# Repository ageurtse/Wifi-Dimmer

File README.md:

# Wifi Dimmer

!!!!! Please do not rebuild this device, in my case there was a serious issue with overheating !!!!!

This is all about my home build WiFi Dimmer
Becaus of it's my first github project, the master is still in Beta. 
For me the project works, but there are a lot off things to change, so keep watching for any change.

11-3-2019, final version, the hard and software is ready to use. 
soon i wil post a youtube movie from live controlling a light. 

This is version 2, in the past i build a differt version which is not exactly what i want. 
Version 2 is one which fit in a simpel housing. 

There are 2 parts of the software, one for the ATTiny and one for the ESP8266
Both are posted here. 
# Word of Caution
Please be very carefull you are working with live voltage 230V, this voltage can realy harm you. 
By building the dimmer, i'm not responsible for any faults or what ever. I stoped development off this dimmer, on one night the triax was overheated. luckely i was at home to prevented real major damage. 

# ATtiny85 Software
The ATtiny85 software is for the soul purpose of dimming the light, there is a zerocross detction which is on interupt 0, the gate is on pin PB3. 
The communication with the main processor is done by softserial. 
The code is based on the forum post at arduino : https://forum.arduino.cc/index.php?topic=314773.0

# ESP8266 software
The main software for the ESP12 module is build with arduino, the wifi and custom settings can be done with the great library from Hieromon https://github.com/Hieromon/AutoConnect
After fist flash by serial, all next updates could be down by browser. 
find the IP-adres or host name and add /update to get to the update page. 
To alter wifi setting's and in the futher mqtt settings and i hope a lot more add /_ac

The file makes use of some thirth party library's which can be found here :
AutoConnect : https://github.com/Hieromon/AutoConnect
PageBuilder : https://github.com/Hieromon/PageBuilder
ArduinoJson : https://arduinojson.org/ version 5

# The hardware
For the main board there is a small mistake made with the Triac, there where 2 wires changes. A1 and A2 need to be turned. 
In a next updat of the print i will fix that, for now i just solderd 2 wires and cross connect them to te pcb.

Also the Fuse holder is to large, i bought a pcb fuse now it all fits well.

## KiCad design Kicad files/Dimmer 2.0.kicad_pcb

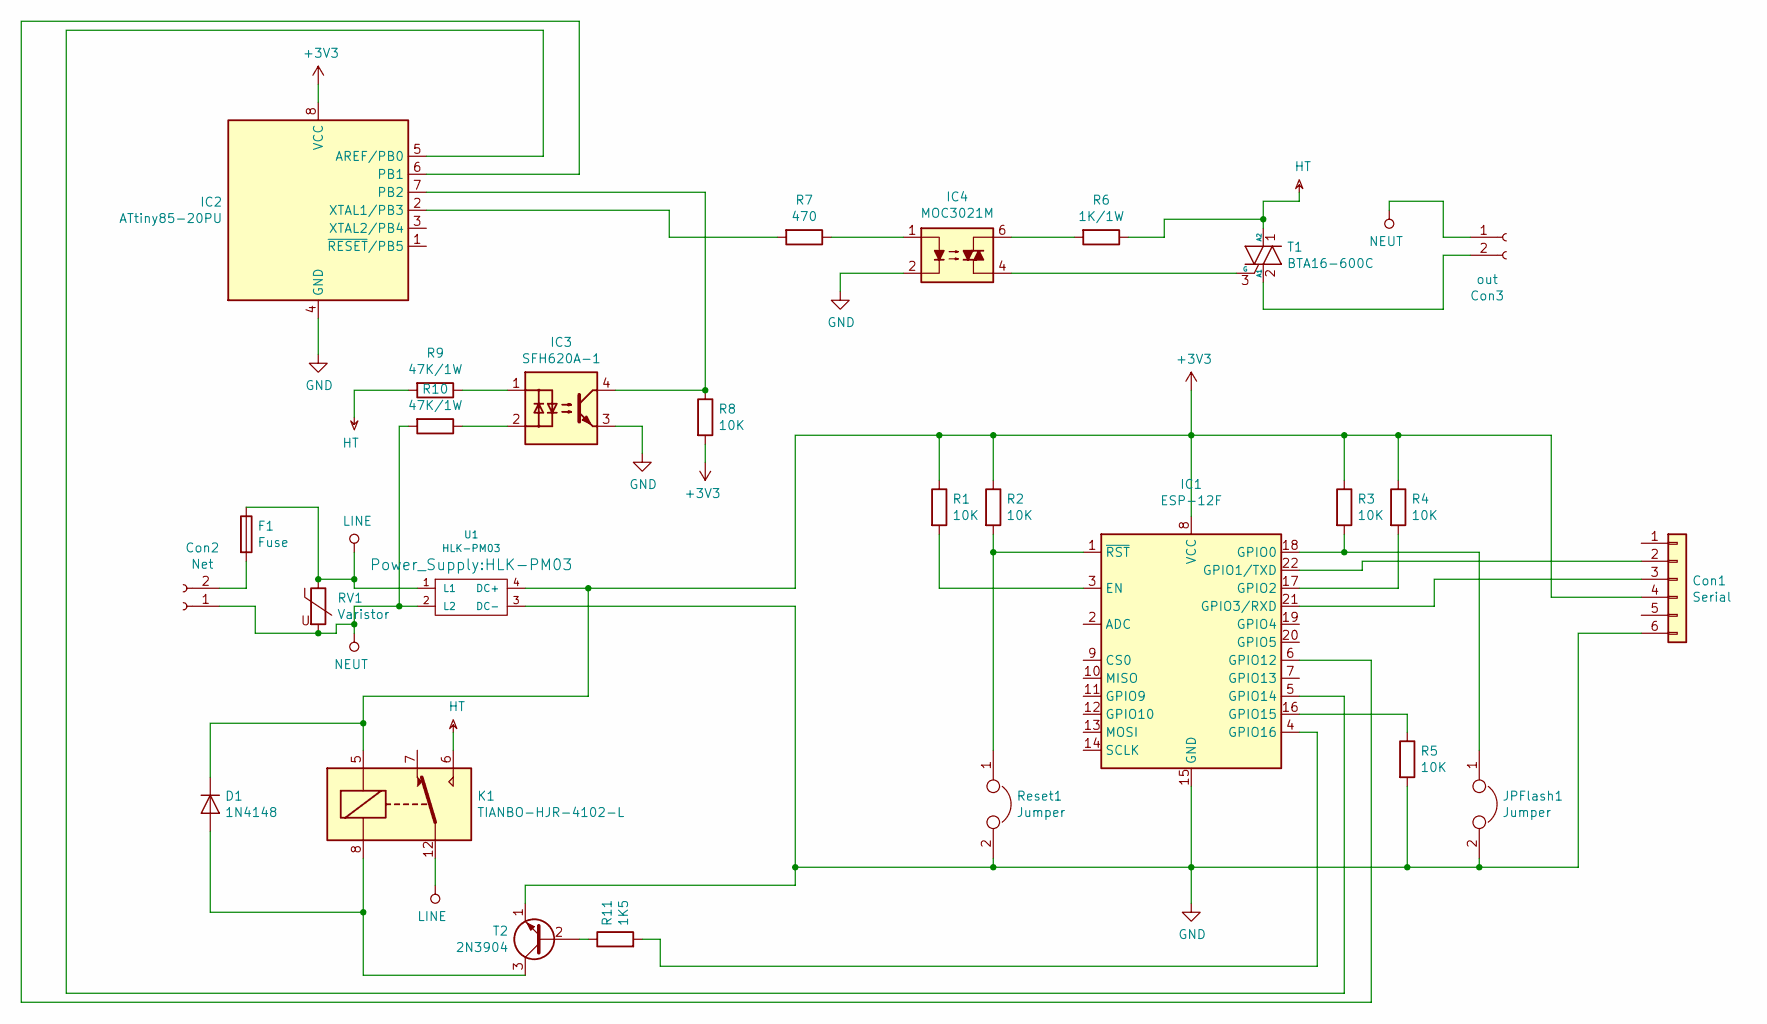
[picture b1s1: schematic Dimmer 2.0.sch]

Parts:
Con1: Serial; PinHeader_1x06_P2.54mm_Vertical
Con2: Net; TerminalBlock_Phoenix_PT-1,5-2-5.0-H_1x02_P5.00mm_Horizontal
Con3: out; TerminalBlock_Phoenix_PT-1,5-2-5.0-H_1x02_P5.00mm_Horizontal
D1: 1N4148; D_DO-35_SOD27_P7.62mm_Horizontal
F1: Fuse; Fuseholder_Cylinder-5x20mm_Stelvio-Kontek_PTF78_Horizontal_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
IC1: ESP-12F; ESP-12E
IC2: ATtiny85-20PU; DIP-8_W7.62mm
IC3: SFH620A-1; DIP-4_W7.62mm
IC4: MOC3021M; DIP-6_W7.62mm
JPFlash1: Jumper; PinHeader_1x02_P2.54mm_Vertical
K1: TIANBO-HJR-4102-L; Relay_SPDT_HJR-4102
R1, R2, R3, R4, R5, R8: 10K; R_1206_3216Metric_Pad1.42x1.75mm_HandSolder
R6: 1K/1W; R_Axial_DIN0414_L11.9mm_D4.5mm_P5.08mm_Vertical
R7: 470; R_1206_3216Metric_Pad1.42x1.75mm_HandSolder
R9, R10: 47K/1W; R_Axial_DIN0414_L11.9mm_D4.5mm_P5.08mm_Vertical
R11: 1K5; R_1206_3216Metric_Pad1.42x1.75mm_HandSolder
RV1: Varistor; RV_Disc_D12mm_W4.8mm_P7.5mm
Reset1: Jumper; PinHeader_1x02_P2.54mm_Vertical
T1: BTA16-600C; TO-220-3_Vertical
T2: 2N3904; TO-92_Inline
U1: HLK-PM03

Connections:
+3V3: Con1.4, D1.1 (K), IC1.8 (VCC), IC2.8 (VCC), K1.5, R1.1, R2.1, R3.1, R4.1, R8.2, U1.4 (DC+)
GND: Con1.6, IC1.15 (GND), IC2.4 (GND), IC3.3, IC4.2, JPFlash1.2, R5.2, Reset1.2, T2.1 (E), U1.3 (DC-)
HT: K1.6, R6.1, R9.2, T1.1 (A2)
LINE: F1.1, K1.12, RV1.1, U1.1 (L1)
NEUT: Con2.1, Con3.1, R10.2, RV1.2, U1.2 (L2)
unnamed: Con1.2, IC1.22 (GPIO1/TXD)
unnamed: Con1.3, IC1.21 (GPIO3/RXD)
unnamed: Con2.2, F1.2
unnamed: Con3.2, T1.2 (A1)
unnamed: D1.2 (A), K1.8, T2.3 (C)
unnamed: IC1.1 (~RST), R2.2, Reset1.1
unnamed: IC1.3 (EN), R1.2
unnamed: IC1.4 (GPIO16), R11.2
unnamed: IC1.5 (GPIO14), IC2.5 (AREF/PB0)
unnamed: IC1.6 (GPIO12), IC2.6 (PB1)
unnamed: IC1.16 (GPIO15), R5.1
unnamed: IC1.17 (GPIO2), R4.2
unnamed: IC1.18 (GPIO0), JPFlash1.1, R3.2
unnamed: IC2.2 (XTAL1/PB3), R7.2
unnamed: IC2.7 (PB2), IC3.4, R8.1
unnamed: IC3.1, R9.1
unnamed: IC3.2, R10.1
unnamed: IC4.1, R7.1
unnamed: IC4.4, T1.3 (G)
unnamed: IC4.6, R6.2
unnamed: R11.1, T2.2 (B)

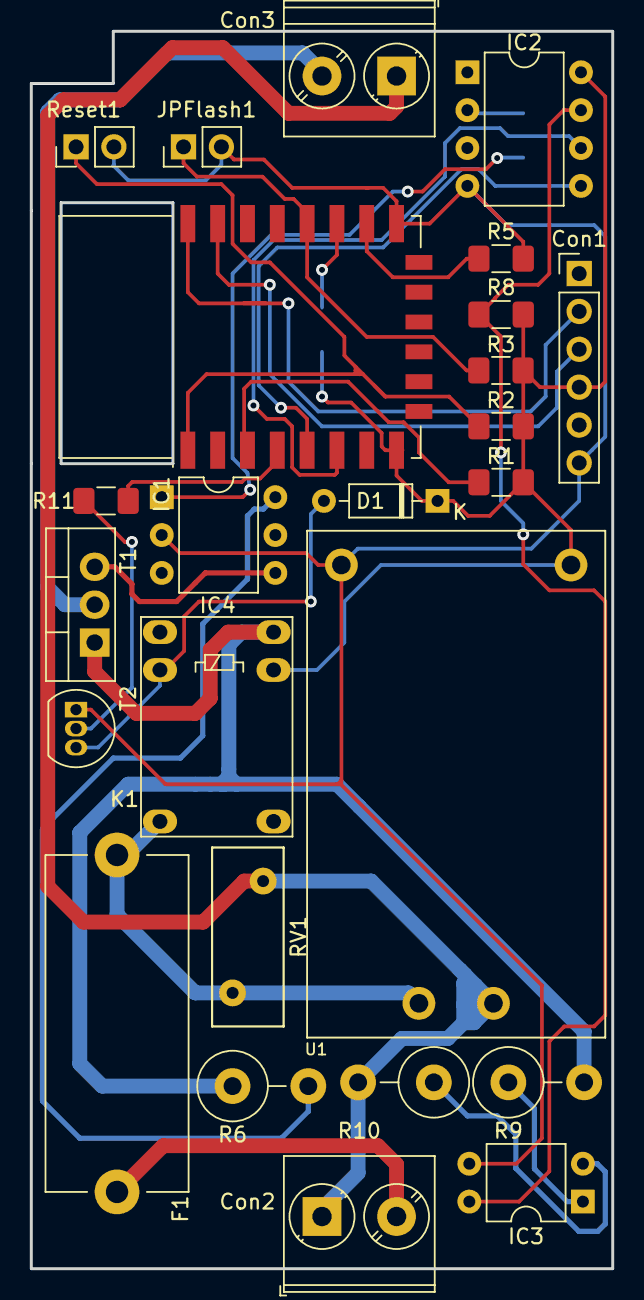
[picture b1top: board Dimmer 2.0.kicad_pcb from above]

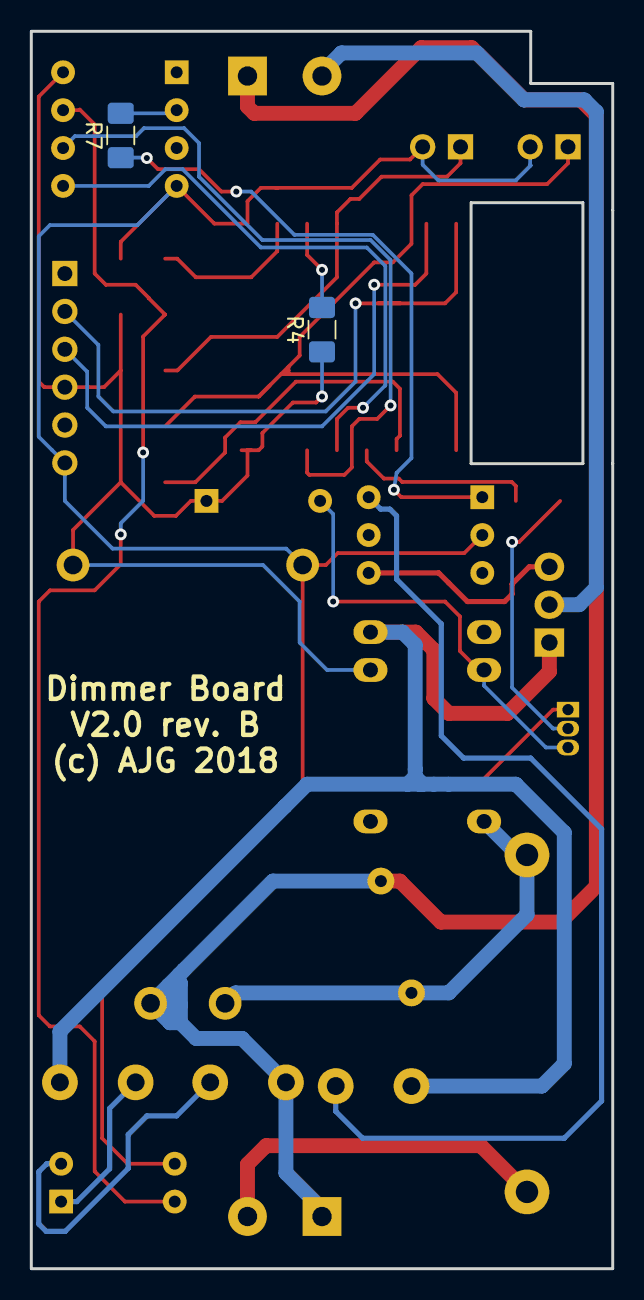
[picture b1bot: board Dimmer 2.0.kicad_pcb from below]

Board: 2 copper layers, 39.0 x 83.0 mm, 27 parts (2 on the bottom side), 26 nets.

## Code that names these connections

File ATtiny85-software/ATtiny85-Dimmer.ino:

// Voltage controlled dimmer with ATtiny85
//
// This arduino sketch includes a zero
// crossing detect function and an opto-isolated triac.
//
// AC Phase control is accomplished using the internal
// hardware timer1 in the ATtiny85
//
// Timing Sequence
// * timer is set up but disabled
// * zero crossing detected
// * timer starts counting from zero
// * comparator set to "delay to on" value
// * counter reaches comparator value
// * comparator ISR turns on triac gate
// * counter set to overflow - pulse width
// * counter reaches overflow
// * overflow ISR turns off triac gate
// * triac stops conducting at next zero cross

// The hardware timer runs at 1MHz (3mA).
// A half period of a 50Hz AC signal takes 10 ms is 10000 counts.
// @ 1MHZ (3ma)prescaler (1000) 128 78 counts per half period

#include <avr/io.h>
#include <avr/interrupt.h>
#include <SoftwareSerial.h>


#define DETECT PB2      //zero cross detect, interrupt 0
#define GATE PB3        //triac gate is physical
#define PULSE 4       	//trigger pulse width 4

#define RX    PB1   		//Serial port RX
#define TX    PB0   		//Serial port TX
SoftwareSerial Serial(RX, TX);

int dimvalue;			//After startup, turn off light;

void setup(){

  delay (9000);								//Wait for booting the ESP8266

	// set up pins
  pinMode(DETECT, INPUT);      //zero cross detect
  digitalWrite(DETECT, HIGH);  //enable pull-up resistor
  pinMode(GATE, OUTPUT);       //triac gate control


  //If all goes well, the light will flash several time, to notify the user
  digitalWrite(GATE, HIGH);
  delay(500);
  digitalWrite(GATE, LOW);
  delay(500);
  digitalWrite(GATE, HIGH);
  delay(500);
  digitalWrite(GATE, LOW);
  delay(500);
  digitalWrite(GATE, HIGH);


  // set up Timer1
  TCCR1 = 0;     											// stop timer
  OCR1A = dimvalue;										// set initial dim value
  TIMSK = _BV(OCIE1A) | _BV(TOIE1);  	// interrupt on Compare Match A | enable timer overflow interrupt
  sei();  														// enable interrupts
  // set up zero crossing interrupt
  attachInterrupt(0,zeroCrossingInterrupt, FALLING);   //

  // ***
  // *** Initialize the Serial port
  // ***
  Serial.begin(9600);
  while (!Serial) {
  }
}

//Interrupt Service Routines
void zeroCrossingInterrupt(){
  TCNT1 = 0;   							//reset timer - count from zero
  TCCR1 = B00001000;        // 1000 ajg 0110 for 64 see table 12.5 of the tiny85 datasheet
}

ISR(TIMER1_COMPA_vect){    //comparator match
  if(OCR1A>95){            //send no pulse to triac for low input voltage for 0v output
    return;
  }

	digitalWrite(GATE,HIGH); //set triac gate to high
  TCNT1 = 255-PULSE;       //trigger pulse width, when TCNT1=255 timer1 overflows
}

ISR(TIMER1_OVF_vect){ 			//timer1 overflow
  digitalWrite(GATE,LOW);   //turn off triac gate
  TCCR1 = 0;                //disable timer stop unintended triggers
}

void loop(){
  if (Serial.available()) {
    // read the most recent byte (which will be from 0 to 100, so it's in %):
  	dimvalue = Serial.read();
  	OCR1A = dimvalue;
  }
}

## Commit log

2019-01-05 Create ATtiny85-Dimmer
    First release of the ATtiny dimmer software, it is based on software from this topic at arduino forum : https://forum.arduino.cc/index.php?topic=314773.0
2019-01-05 Update README.md
    add image
2019-01-05 Power on, Light off
    Final attiny software.
    The light will now go off after the module is powerd up.
2019-01-05 Add Kicad Project files
    All my current Kicad files
2019-01-05 Add ESP software
    Main ESP software
2019-01-05 Work in progress
2019-01-05 Add extension
2019-01-05 Made relais switch
    If minimal dim is reached, turn off power by switching relais off, else turn on relais.
    In a next relais, if relais is turned on, gif a max puls for led lights
2019-03-08 Rewrite project with arduino
    Rewrite project with Arduino
    The esp8266 files are in Dimmer_3.0
2019-03-08 typo's and formating
2019-03-08 small update in custom webpage
    Small update in custom webage and file handeling, all variables are now visible.
2019-03-08 Small changes
    When first flash, the config file is now correct created.
    When a device name is set, this is also the hostename.
2019-03-08 add webupdate
2019-03-08 typo
2019-03-09 alterd welcom screen
2019-03-11 mqtt added
    Today i finished the project, mqtt is added.
2019-03-13 small performance update
2019-04-25 New developed board.
2019-08-25 resetup new version
2019-08-26 new version, updated PCB
2019-08-31 partial schematic
